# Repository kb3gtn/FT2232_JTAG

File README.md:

# FT2232_JTAG
 FT2232 JTAG/SPI/UART/GPIO board

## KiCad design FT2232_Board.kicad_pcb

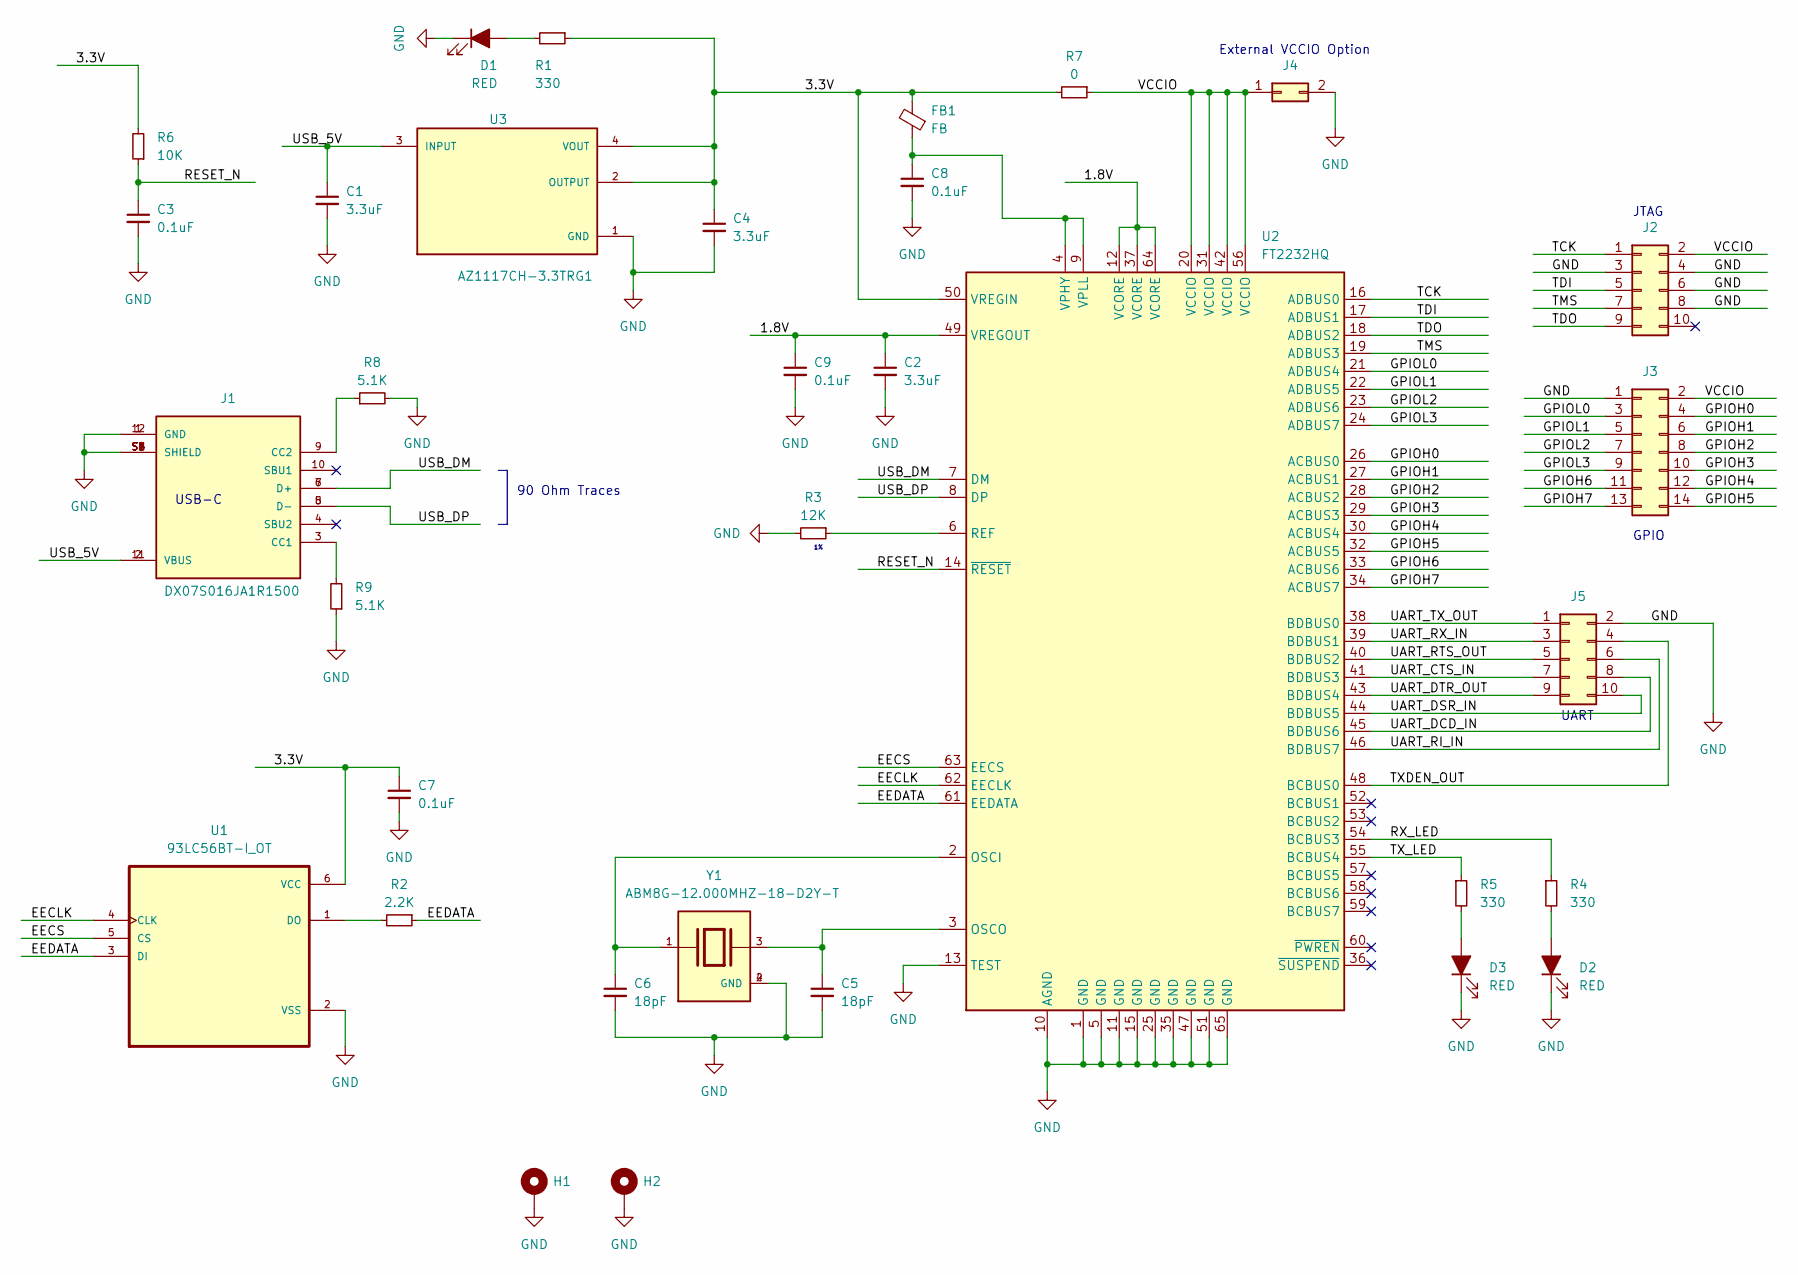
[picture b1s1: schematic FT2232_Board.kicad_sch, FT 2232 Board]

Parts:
C1, C2, C4: 3.3uF; C_0603_1608Metric_Pad1.08x0.95mm_HandSolder
C3, C7, C8, C9: 0.1uF; C_0603_1608Metric_Pad1.08x0.95mm_HandSolder
C5, C6: 18pF; C_0402_1005Metric_Pad0.74x0.62mm_HandSolder
D1, D2, D3: RED; D_0603_1608Metric_Pad1.05x0.95mm_HandSolder
FB1: FB; R_0402_1005Metric_Pad0.72x0.64mm_HandSolder; Manufacturer Part Number 100 Ohm @ 100 MHz
H1, H2: MountingHole_Pad; MountingHole_2.7mm_M2.5_Pad_Via
J1: DX07S016JA1R1500; JAE_DX07S016JA1R1500; PARTREV 1
J2, J5: Conn_02x05_Odd_Even; PinHeader_2x05_P2.54mm_Vertical; Manufacturer Part Number Generic
J3: Conn_02x07_Odd_Even; PinHeader_2x07_P2.54mm_Vertical; Manufacturer Part Number Generic
J4: Conn_02x01; PinHeader_2x01_P2.54mm_Vertical; Manufacturer Part Number Generic
R1, R4, R5: 330; R_0603_1608Metric_Pad0.98x0.95mm_HandSolder
R2: 2.2K; R_0603_1608Metric_Pad0.98x0.95mm_HandSolder
R3: 12K; R_0603_1608Metric_Pad0.98x0.95mm_HandSolder
R6: 10K; R_0603_1608Metric_Pad0.98x0.95mm_HandSolder
R7: 0; R_0603_1608Metric_Pad0.98x0.95mm_HandSolder
R8, R9: 5.1K; R_0603_1608Metric_Pad0.98x0.95mm_HandSolder
U1: 93LC56BT-I_OT; SOT95P280X145-6N; Manufacturer Part Number 93LC56BT-I/OT
U2: FT2232HQ; QFN-64-1EP_9x9mm_P0.5mm_EP4.35x4.35mm; Manufacturer Part Number FT2232HQ
U3: AZ1117CH-3.3TRG1; DIODES_AZ1117CH-3.3TRG1_0; MOUSER_PART_NUMBER 621-AZ1117CH-3.3TRG1; MOUSER_DESCRIPTION LDO Voltage Regulators LDO BJT HiCurr 1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
Y1: ABM8G-12.000MHZ-18-D2Y-T; XTAL_ABM8G-12.000MHZ-18-D2Y-T; PARTREV 08.13.15

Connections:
/1.8V: C2.1, C9.1, U2.12 (VCORE), U2.37 (VCORE), U2.49 (VREGOUT), U2.64 (VCORE)
/3.3V: C4.1, C7.1, FB1.2, R1.1, R6.2, R7.2, U1.6 (VCC), U2.50 (VREGIN), U3.2 (OUTPUT), U3.4 (VOUT)
/EECLK: U1.4 (CLK), U2.62 (EECLK)
/EECS: U1.5 (CS), U2.63 (EECS)
/EEDATA: R2.1, U1.3 (DI), U2.61 (EEDATA)
/GPIOH0: J3.4, U2.26 (ACBUS0)
/GPIOH1: J3.6, U2.27 (ACBUS1)
/GPIOH2: J3.8, U2.28 (ACBUS2)
/GPIOH3: J3.10, U2.29 (ACBUS3)
/GPIOH4: J3.12, U2.30 (ACBUS4)
/GPIOH5: J3.14, U2.32 (ACBUS5)
/GPIOH6: J3.11, U2.33 (ACBUS6)
/GPIOH7: J3.13, U2.34 (ACBUS7)
/GPIOL0: J3.3, U2.21 (ADBUS4)
/GPIOL1: J3.5, U2.22 (ADBUS5)
/GPIOL2: J3.7, U2.23 (ADBUS6)
/GPIOL3: J3.9, U2.24 (ADBUS7)
/RESET_N: C3.1, R6.1, U2.14 (~RESET)
/RX_LED: R4.1, U2.54 (BCBUS3)
/TCK: J2.1, U2.16 (ADBUS0)
/TDI: J2.5, U2.17 (ADBUS1)
/TDO: J2.9, U2.18 (ADBUS2)
/TMS: J2.7, U2.19 (ADBUS3)
/TXDEN_OUT: J5.4, U2.48 (BCBUS0)
/TX_LED: R5.1, U2.55 (BCBUS4)
/UART_CTS_IN: J5.7, U2.41 (BDBUS3)
/UART_DCD_IN: J5.8, U2.45 (BDBUS6)
/UART_DSR_IN: J5.10, U2.44 (BDBUS5)
/UART_DTR_OUT: J5.9, U2.43 (BDBUS4)
/UART_RI_IN: J5.6, U2.46 (BDBUS7)
/UART_RTS_OUT: J5.5, U2.40 (BDBUS2)
/UART_RX_IN: J5.3, U2.39 (BDBUS1)
/UART_TX_OUT: J5.1, U2.38 (BDBUS0)
/USB_5V: C1.1, J1.2 (VBUS), J1.11 (VBUS), U3.3 (INPUT)
/USB_DM: J1.6 (D+), J1.7 (D+), U2.7 (DM)
/USB_DP: J1.5 (D-), J1.8 (D-), U2.8 (DP)
/VCCIO: J2.2, J3.2, J4.1, R7.1, U2.20 (VCCIO), U2.31 (VCCIO), U2.42 (VCCIO), U2.56 (VCCIO)
GND: C1.2, C2.2, C3.2, C4.2, C5.2, C6.2, C7.2, C8.2, C9.2, D1.1 (K), D2.1 (K), D3.1 (K), H1.1, H2.1, J1.1 (GND), J1.12 (GND), J1.S1 (SHIELD), J1.S2 (SHIELD), J1.S3 (SHIELD), J1.S4 (SHIELD), J1.S5 (SHIELD), J1.S6 (SHIELD), J2.3, J2.4, J2.6, J2.8, J3.1, J4.2, J5.2, R3.2, R8.2, R9.1, U1.2 (VSS), U2.1 (GND), U2.5 (GND), U2.10 (AGND), U2.11 (GND), U2.13 (TEST), U2.15 (GND), U2.25 (GND), U2.35 (GND), U2.47 (GND), U2.51 (GND), U2.65 (GND), U3.1 (GND), Y1.2 (GND), Y1.4 (GND)
unnamed: D3.2 (A), R5.2
unnamed: D2.2 (A), R4.2
unnamed: D1.2 (A), R1.2
unnamed: J1.3 (CC1), R9.2
unnamed: J1.9 (CC2), R8.1
unnamed: C6.1, U2.2 (OSCI), Y1.1
unnamed: C5.1, U2.3 (OSCO), Y1.3
unnamed: R3.1, U2.6 (REF)
unnamed: C8.1, FB1.1, U2.4 (VPHY), U2.9 (VPLL)
unnamed: R2.2, U1.1 (DO)

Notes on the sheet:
JTAG
90 Ohm Traces
UART
External VCCIO Option
GPIO
USB-C

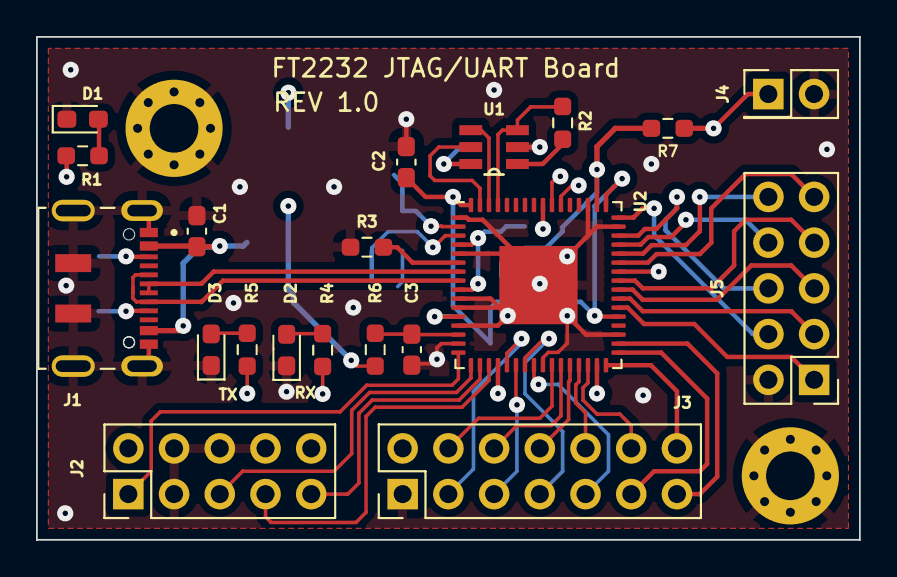
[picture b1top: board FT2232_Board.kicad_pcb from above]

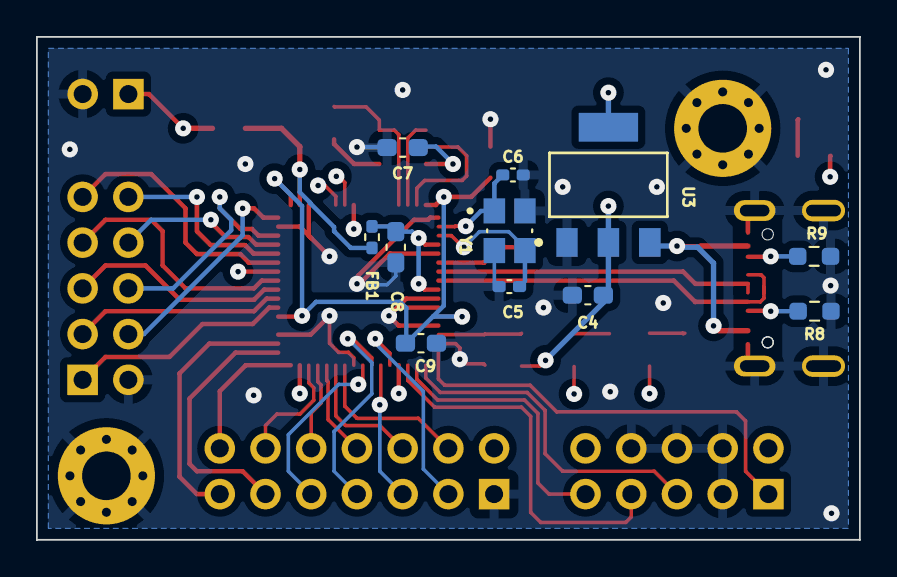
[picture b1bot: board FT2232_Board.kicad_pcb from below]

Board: 4 copper layers, 45.7 x 27.9 mm, 33 parts (11 on the bottom side), 48 nets.

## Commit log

2023-11-22 Initial Checkin
    Initial Checkin
2023-11-22 Added pdf schematic
    added PDF schematic
